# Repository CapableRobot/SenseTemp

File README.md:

# SenseTemp

Designed by [Capable Robot Components](http://capablerobot.com).  
Follow us on [Twitter](http://twitter.com/capablerobot) for product announcements and updates.

---

**SenseTemp is available on [CrowdSupply](https://www.crowdsupply.com/capable-robot-components/sensetemp) & [Mouser](https://www.mouser.com/Search/Refine?Keyword=sensetemp).  Please visit the [campaign page](https://www.crowdsupply.com/capable-robot-components/sensetemp) or [Mouser](https://www.mouser.com/ProductDetail/Crowd-Supply/cs-sensetemp-01?qs=sGAEpiMZZMsSgQ5oX0A7uhzs7btMGoRQjdDbb5Xc%2F1l7fRq91ffQkQ%3D%3D) for product information and to purchase SenseTemp.** 

SenseTemp provides four highly accurate and flexible temperature sensors which allow you to understand the operation of your:

* Mobile robot
* Embedded system 
* Double pane windows on your house
* Home brewing operation
* Or any other system where temperature and thermal conduction is important

It's designed for quick tests as well as long-duration process monitoring.

## SenseTemp Features 

* **Small:** so that it can be on a mobile system being tested.  The RTDs themselves are 2 mm x 4 mm, making them thermally responsive and great for measurement of point heat sources
* **Inexpensive:** allowing many points of temperature monitoring
* **Battery Powered:** including LiPoly & USB power banks
* **Wireless:** to make test setup faster and more flexible
* **Open Software:** so that the device can directly feed data into a data logging system of your choice
* **Open Hardware:** to enable derivative designs and for easy hacking

## Specifications

|Feature|Specification|
|----|----|
|Sensors|4x Platinum resistance temperature detectors (RTDs)|
|RTD Accuracy|±0.15°C|
|Temperature Range|-50°C to 260°C|
|Interface ICs|4x [MAX31865](https://www.maximintegrated.com/en/products/sensors/MAX31865.html) with 4 wire sensing|
|Form Factor|[Adafruit Feather](https://www.adafruit.com/feather)|
|Dimensions|0.9" x 2.4"|

## Feather Hosts

SenseTemp is designed to mate with Adafruit Feather-compatible host modules, like:

* [Adafruit Feather M4 Express](https://www.adafruit.com/product/3857)
* [Adafruit Feather M0 Express](https://www.adafruit.com/product/3403)
* [Adafruit ESP32 Feather Host](https://www.adafruit.com/product/3405)
* [Adafruit HalloWing](https://www.adafruit.com/product/3900)

Note that the ES8266 Feather is **NOT** supported due to the limited IO on the ESP8266.  It does not have enough pins to support the four SPI devices of the SenseTemp.

## Software

The software running on the Feather host processor does change based on the feather host you are using.  This repository contains software for:

* [**CircuitPython:**](software-circuitpython) if you are using a Cortex M4 or M0 Feather.  
* [**MicroPython:**](software-micropython) if you are using an ESP32 Feather.  The ESP32 is not currently supported by CircuitPython.

## Hardware Revisions

* [CREAES](revisions/CREAES) : Last release 2018-10-18.
	* Changed from 0805 to 0603 passive components.
	* Moved all components to top side of PCB.
	* Changed license from **CC BY-SA 4.0** to **CERN OHL v1.2**.
	* Can be powered from either USB or Li-Ion sources.
* [X9EG](revisions/X9EG) : Released 2018-08-28.
	* Added `SIO` pin with AT21CS01 1-Wire EEPROM for configuration & serialization.
	* Added `EN` pin to allow host PCB to disable 5v to 3v regulator on this PCB.
	* Changed RTD connector from 20 pin (used on XTMT version) to 16 pin.
* [XTMT](revisions/XTMT) : Initial version released 2018-05-18.

## License Information

| **Type** | **License** |
| --- | --- |
| Hardware | Copyright Capable Robot Components 2018 <br><br>This documentation describes Open Hardware and is licensed under the [CERN OHL v1.2 or later](https://www.ohwr.org/licenses/cern-ohl/license_versions/v1.2). <br/><br/> You may redistribute and modify this documentation under the terms of the CERN OHL v.1.2.  This documentation is distributed WITHOUT ANY EXPRESS OR IMPLIED WARRANTY, INCLUDING OF MERCHANTABILITY, SATISFACTORY QUALITY AND FITNESS FOR A PARTICULAR PURPOSE. Please see the CERN OHL v.1.2 for applicable conditions |
| Software | [MIT License](LICENSE.txt) |
| Documentation | [Creative Commons Attribution-ShareAlike](https://creativecommons.org/licenses/by-sa/4.0/) License |

More detailed information about the CERN License is available in the [license](license) folder and on the [CERN website](https://www.ohwr.org/projects/cernohl/wiki).

| **OSHW Certification** |
| --- |
|  | 
| [Certified open source hardware](https://certification.oshwa.org/us000151.html) by the [Open Source Hardware Association](https://www.oshwa.org) |

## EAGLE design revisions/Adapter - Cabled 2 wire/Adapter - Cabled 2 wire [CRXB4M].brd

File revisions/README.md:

# SenseTemp Hardware Revisions

Designed by [Capable Robot Components](http://capablerobot.com).  
Follow us on [Twitter](http://twitter.com/capablerobot) for product announcements and updates.

---

**SenseTemp is available on [CrowdSupply](https://www.crowdsupply.com/capable-robot-components/sensetemp) & [Mouser](https://www.mouser.com/Search/Refine?Keyword=sensetemp).  Please visit the [campaign page](https://www.crowdsupply.com/capable-robot-components/sensetemp) or [Mouser](https://www.mouser.com/ProductDetail/Crowd-Supply/cs-sensetemp-01?qs=sGAEpiMZZMsSgQ5oX0A7uhzs7btMGoRQjdDbb5Xc%2F1l7fRq91ffQkQ%3D%3D) for product information and to purchase SenseTemp.** 

---

* [CREAES](revisions/CREAES) : Last release 2018-10-18.
	* Changed from 0805 to 0603 passive components.
	* Moved all components to top side of PCB.
	* Changed license from **CC BY-SA 4.0** to **CERN OHL v1.2**.
	* Can be powered from either USB or Li-Ion sources.
* [X9EG](revisions/X9EG) : Released 2018-08-28.
	* Added `SIO` pin with AT21CS01 1-Wire EEPROM for configuration & serialization.
	* Added `EN` pin to allow host PCB to disable 5v to 3v regulator on this PCB.
	* Changed RTD connector from 20 pin (used on XTMT version) to 16 pin.
* [XTMT](revisions/XTMT) : Initial version released 2018-05-18.

---

Also in this folder are two adapter PCBs which allows SenseTemp's 50mil (4x 4-wire) connector to be adapted to 4x 2-way 5mm screw terminals, allowing SenseTemp to use 2-wire and 3-wire (in 2-wire mode) P1000 RTDs.

The 'stacking' design has the same outline and mounting as SenseTemp and is designed to stack vertically above SenseTemp using a [AMP Minitek 20021321-00016C4LF](https://octopart.com/20021321-00016c4lf-amphenol+icc+%2F+fci-12642443?r=sp) (or similar) connector.

The 'cabled' design is smaller and cabled to SenseTemp via a 16 conductor, 50 mil ribbon cabled.  The recommended 16 pin connector for it is [CNC Tech 3221-16-0300-00](https://octopart.com/3221-16-0300-00-cnc+tech-47114357?r=sp) or similar.

Bare PCBs (e.g. no components installed or included) are available for purchase directly from OSHPark:

| [Cabled Adapter](https://oshpark.com/shared_projects/WjlpBAlQ) | [Stacking Adapter](https://oshpark.com/shared_projects/11pGTiwa) |
|---|---|
||  |

---

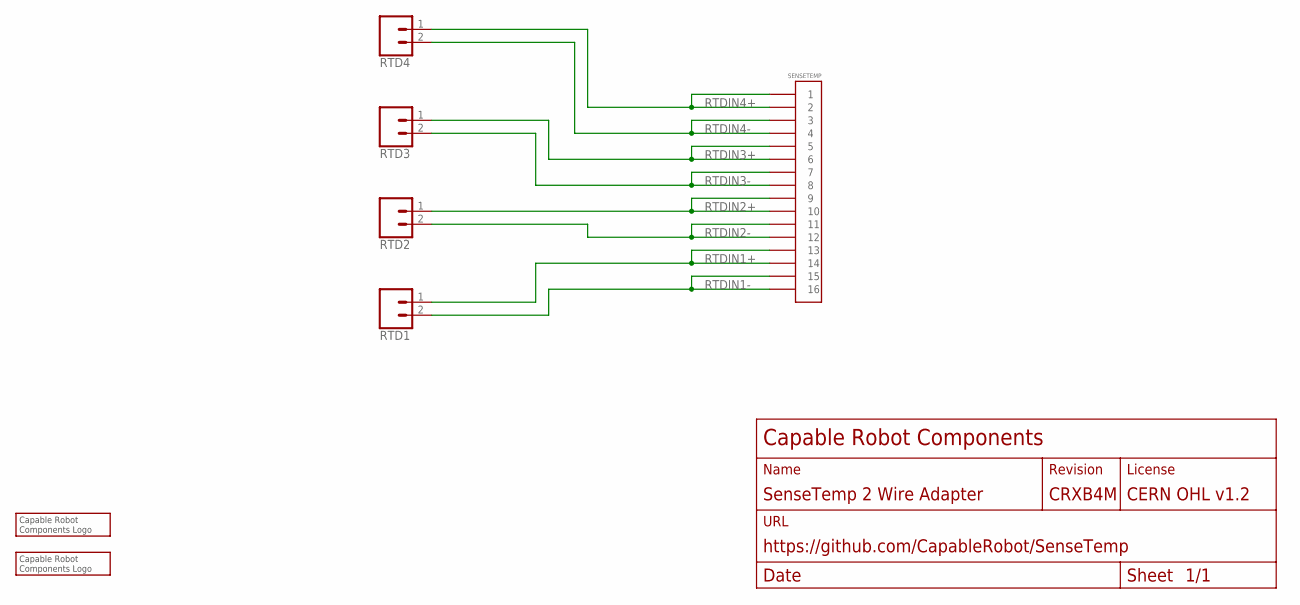
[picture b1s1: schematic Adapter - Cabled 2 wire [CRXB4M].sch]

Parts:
LOGO1: CRC-LOGO7SILK; CRC-LOGO-7-SILK
LOGO2: CRC-LOGO5; CRC-LOGO-5
RTD1, RTD2, RTD3, RTD4: CONN_025MM; SCREWTERMINAL-5MM-2
SENSETEMP: CONN-16ZT; CONN-2X8-050-SMT-ZT; MPN 3221-16-0300-00

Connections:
RTDIN1+: RTD1.1, SENSETEMP.13, SENSETEMP.14
RTDIN1-: RTD1.2, SENSETEMP.15, SENSETEMP.16
RTDIN2+: RTD2.1, SENSETEMP.9, SENSETEMP.10
RTDIN2-: RTD2.2, SENSETEMP.11, SENSETEMP.12
RTDIN3+: RTD3.1, SENSETEMP.5, SENSETEMP.6
RTDIN3-: RTD3.2, SENSETEMP.7, SENSETEMP.8
RTDIN4+: RTD4.1, SENSETEMP.1, SENSETEMP.2
RTDIN4-: RTD4.2, SENSETEMP.3, SENSETEMP.4

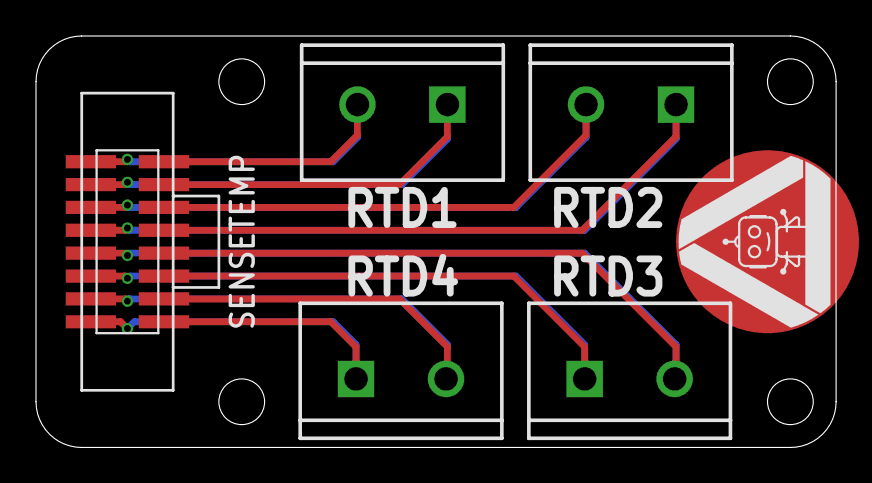
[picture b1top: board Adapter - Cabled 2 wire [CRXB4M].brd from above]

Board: 2 copper layers, 44.5 x 22.9 mm, 7 parts (1 on the bottom side), 8 nets.

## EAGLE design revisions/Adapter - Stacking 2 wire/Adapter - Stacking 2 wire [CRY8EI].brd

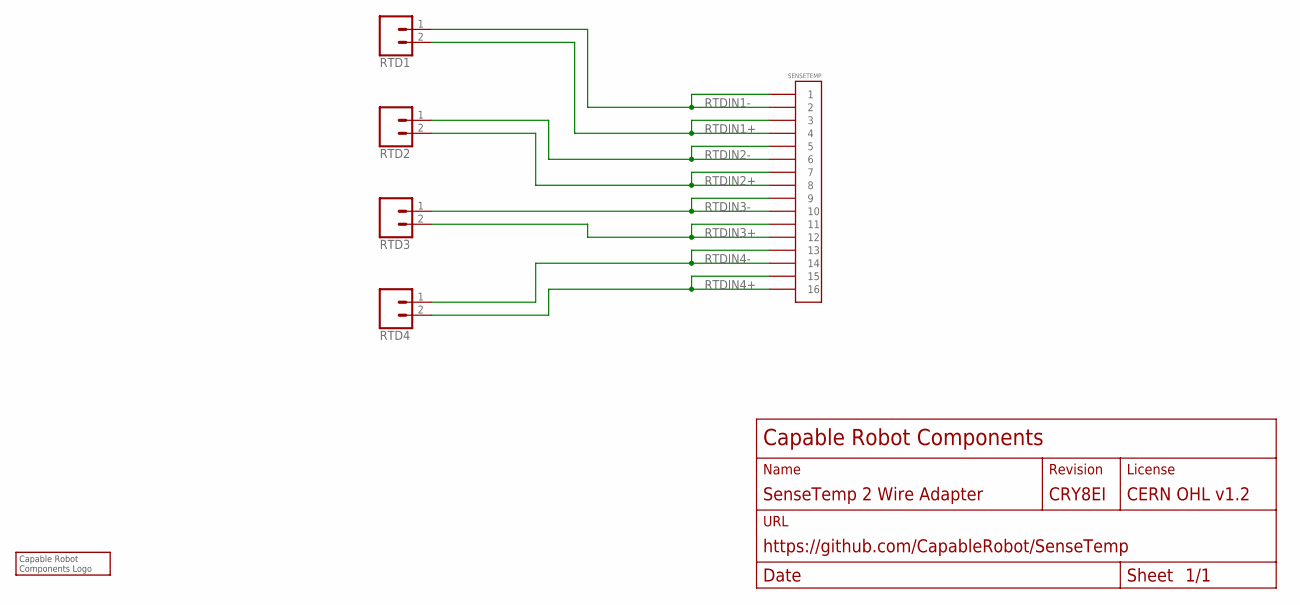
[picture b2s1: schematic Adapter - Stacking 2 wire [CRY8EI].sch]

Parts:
LOGO1: CRC-LOGO7SILK; CRC-LOGO-7-SILK
RTD1, RTD2, RTD3, RTD4: CONN_025MM; SCREWTERMINAL-5MM-2
SENSETEMP: CONN-16ZT; CONN-2X8-050-SMT-ZT; MPN 3221-16-0300-00

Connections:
RTDIN1+: RTD1.2, SENSETEMP.3, SENSETEMP.4
RTDIN1-: RTD1.1, SENSETEMP.1, SENSETEMP.2
RTDIN2+: RTD2.2, SENSETEMP.7, SENSETEMP.8
RTDIN2-: RTD2.1, SENSETEMP.5, SENSETEMP.6
RTDIN3+: RTD3.2, SENSETEMP.11, SENSETEMP.12
RTDIN3-: RTD3.1, SENSETEMP.9, SENSETEMP.10
RTDIN4+: RTD4.2, SENSETEMP.15, SENSETEMP.16
RTDIN4-: RTD4.1, SENSETEMP.13, SENSETEMP.14

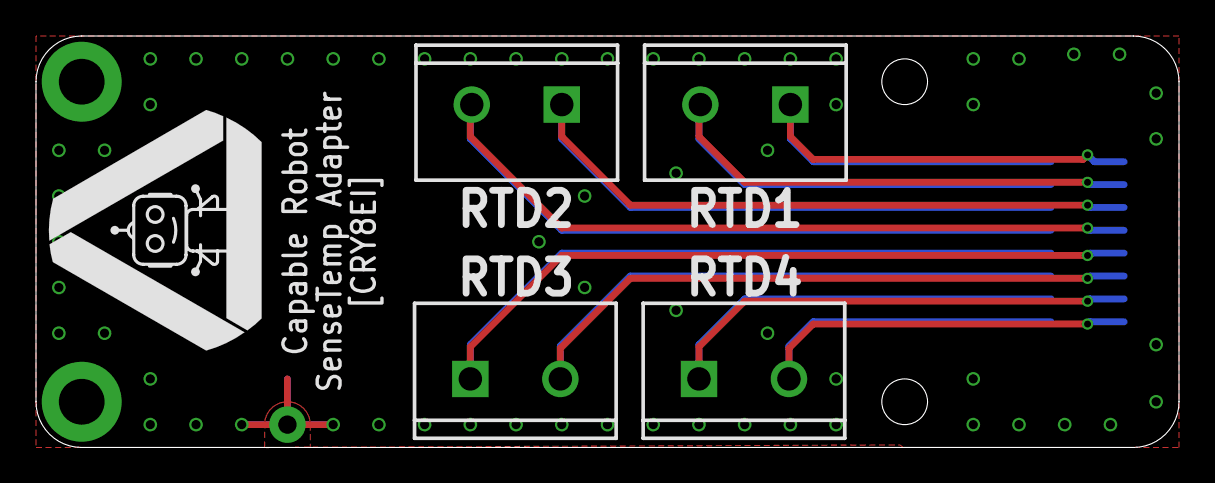
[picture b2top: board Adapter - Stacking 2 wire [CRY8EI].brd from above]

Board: 2 copper layers, 63.5 x 22.9 mm, 6 parts (1 on the bottom side), 8 nets.

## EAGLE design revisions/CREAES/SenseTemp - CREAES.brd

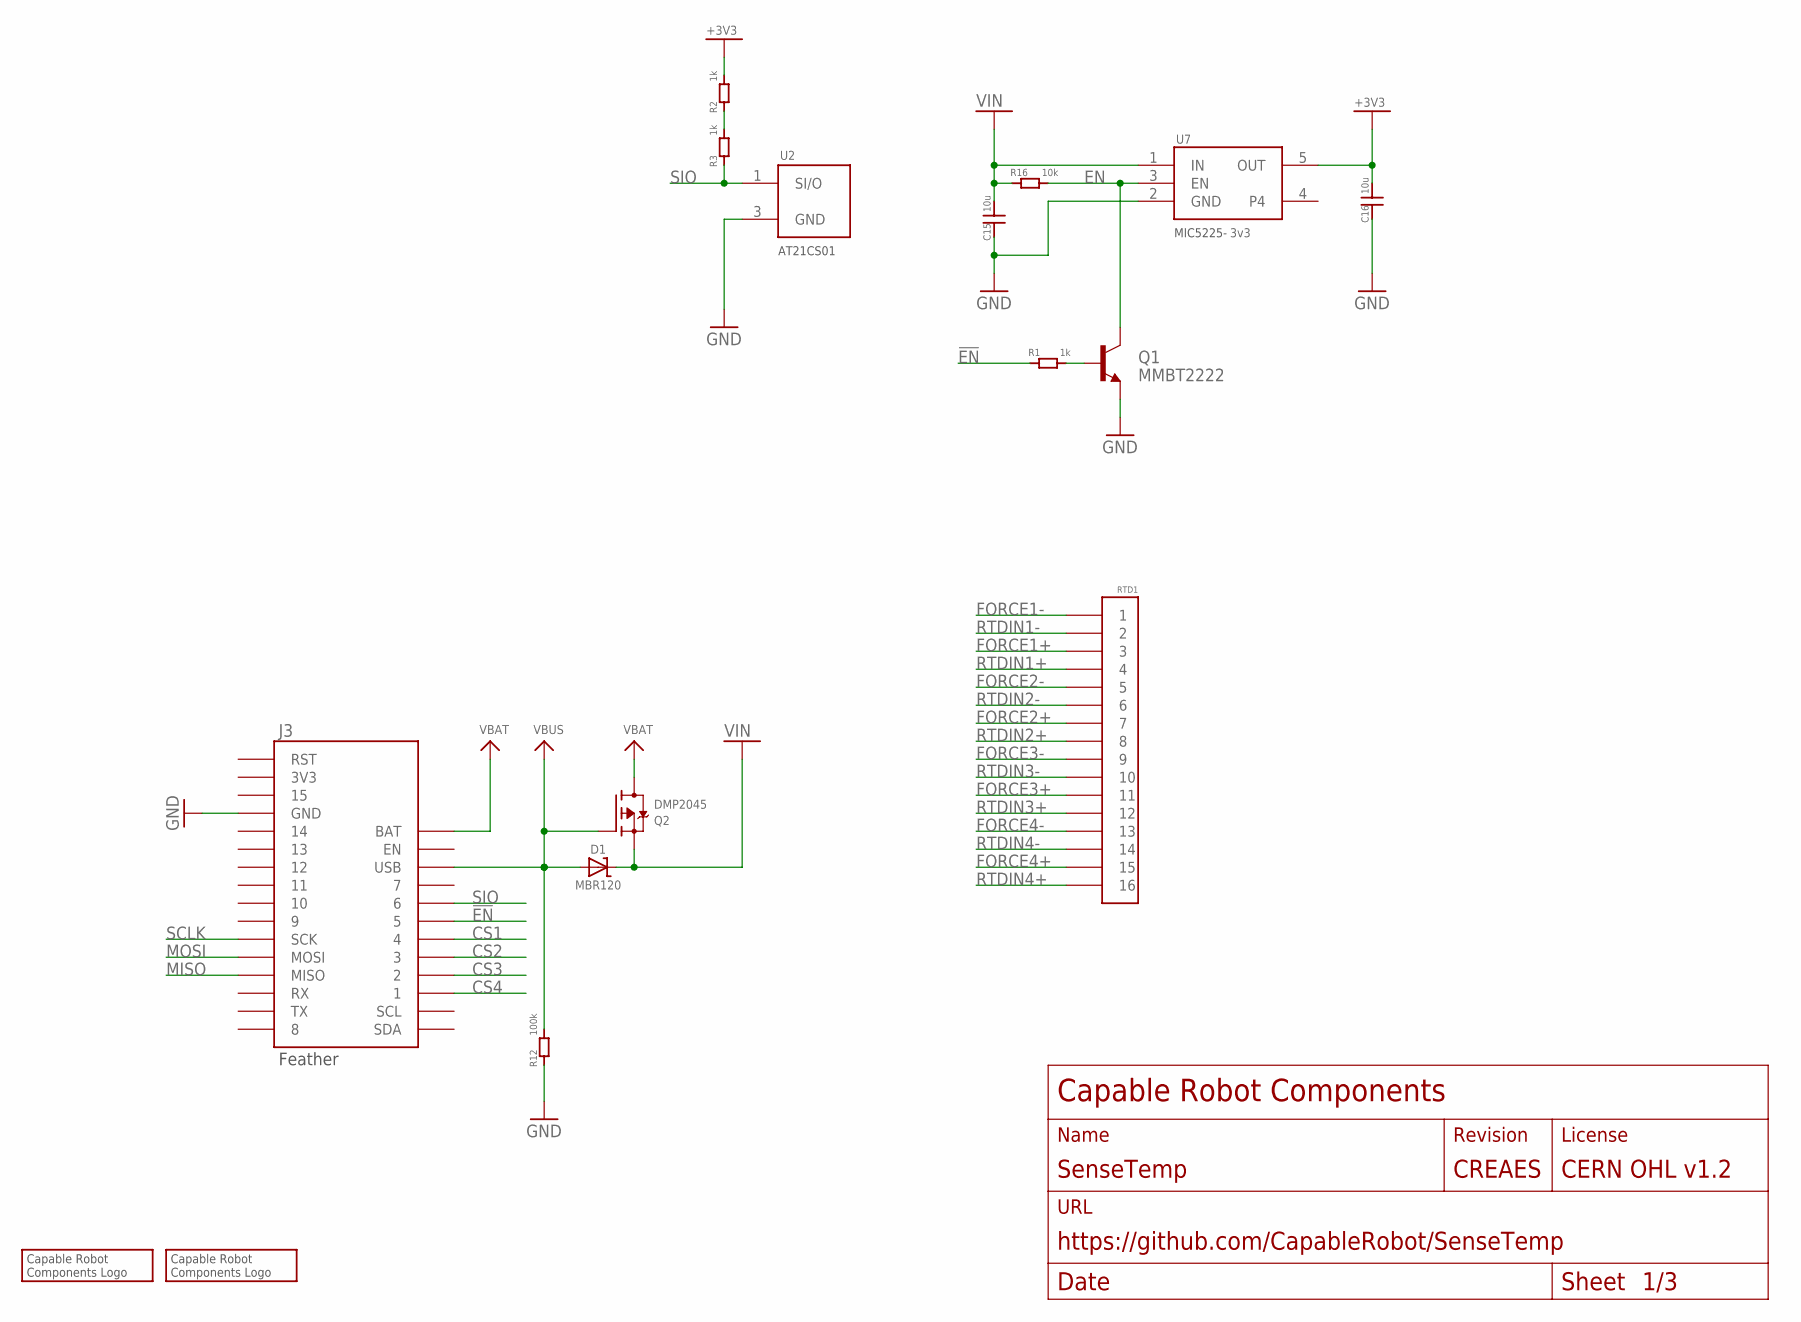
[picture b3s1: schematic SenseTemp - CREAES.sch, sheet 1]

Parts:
C15, C16: 10u; 0805
D1: MBR120; SOD-123; MPN MBR120VLSFT3G
J3: FEATHERPTH; FEATHER-PTH
LOGO1: CRC-LOGO7SILK; CRC-LOGO-7-SILK
LOGO2: CRC-LOGO5; CRC-LOGO-5
Q1: MMBT2222; SOT23-3; MPN MMBT2222LT1G
Q2: DMP2045; SOT23-R; MPN DMP2045U-7
R1, R2, R3: 1k; 0603
R12: 100k; 0603
R16: 10k; 0603
RTD1: CONN-16ZT; CONN-2X8-050-SMT-ZT; MPN 3221-16-0300-00
U2: AT21CS01; SOT23
U7: 3v3; SOT25

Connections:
!EN: J3.5, R1.1
+3V3: C16.2, R2.2, U7.5 (OUT); also elsewhere on the board
CS1: J3.4; also elsewhere on the board
CS2: J3.3; also elsewhere on the board
CS3: J3.2; also elsewhere on the board
CS4: J3.1; also elsewhere on the board
EN: Q1.3 (C), R16.2, U7.3 (EN)
FORCE1+: RTD1.3; also elsewhere on the board
FORCE1-: RTD1.1; also elsewhere on the board
FORCE2+: RTD1.7; also elsewhere on the board
FORCE2-: RTD1.5; also elsewhere on the board
FORCE3+: RTD1.11; also elsewhere on the board
FORCE3-: RTD1.9; also elsewhere on the board
FORCE4+: RTD1.15; also elsewhere on the board
FORCE4-: RTD1.13; also elsewhere on the board
GND: C15.1, C16.1, J3.GND, Q1.2 (E), R12.1, U2.3 (GND), U7.2 (GND); also elsewhere on the board
MISO: J3.MISO; also elsewhere on the board
MOSI: J3.MOSI; also elsewhere on the board
unnamed: R2.1, R3.2
unnamed: Q1.1 (B), R1.2
RTDIN1+: RTD1.4; also elsewhere on the board
RTDIN1-: RTD1.2; also elsewhere on the board
RTDIN2+: RTD1.8; also elsewhere on the board
RTDIN2-: RTD1.6; also elsewhere on the board
RTDIN3+: RTD1.12; also elsewhere on the board
RTDIN3-: RTD1.10; also elsewhere on the board
RTDIN4+: RTD1.16; also elsewhere on the board
RTDIN4-: RTD1.14; also elsewhere on the board
SCLK: J3.SCK; also elsewhere on the board
SIO: J3.6, R3.1, U2.1 (SI/O)
VBAT: J3.BAT, Q2.3 (D)
VBUS: D1.A, J3.USB, Q2.1 (G), R12.2
VIN: C15.2, D1.C, Q2.2 (S), R16.1, U7.1 (IN)

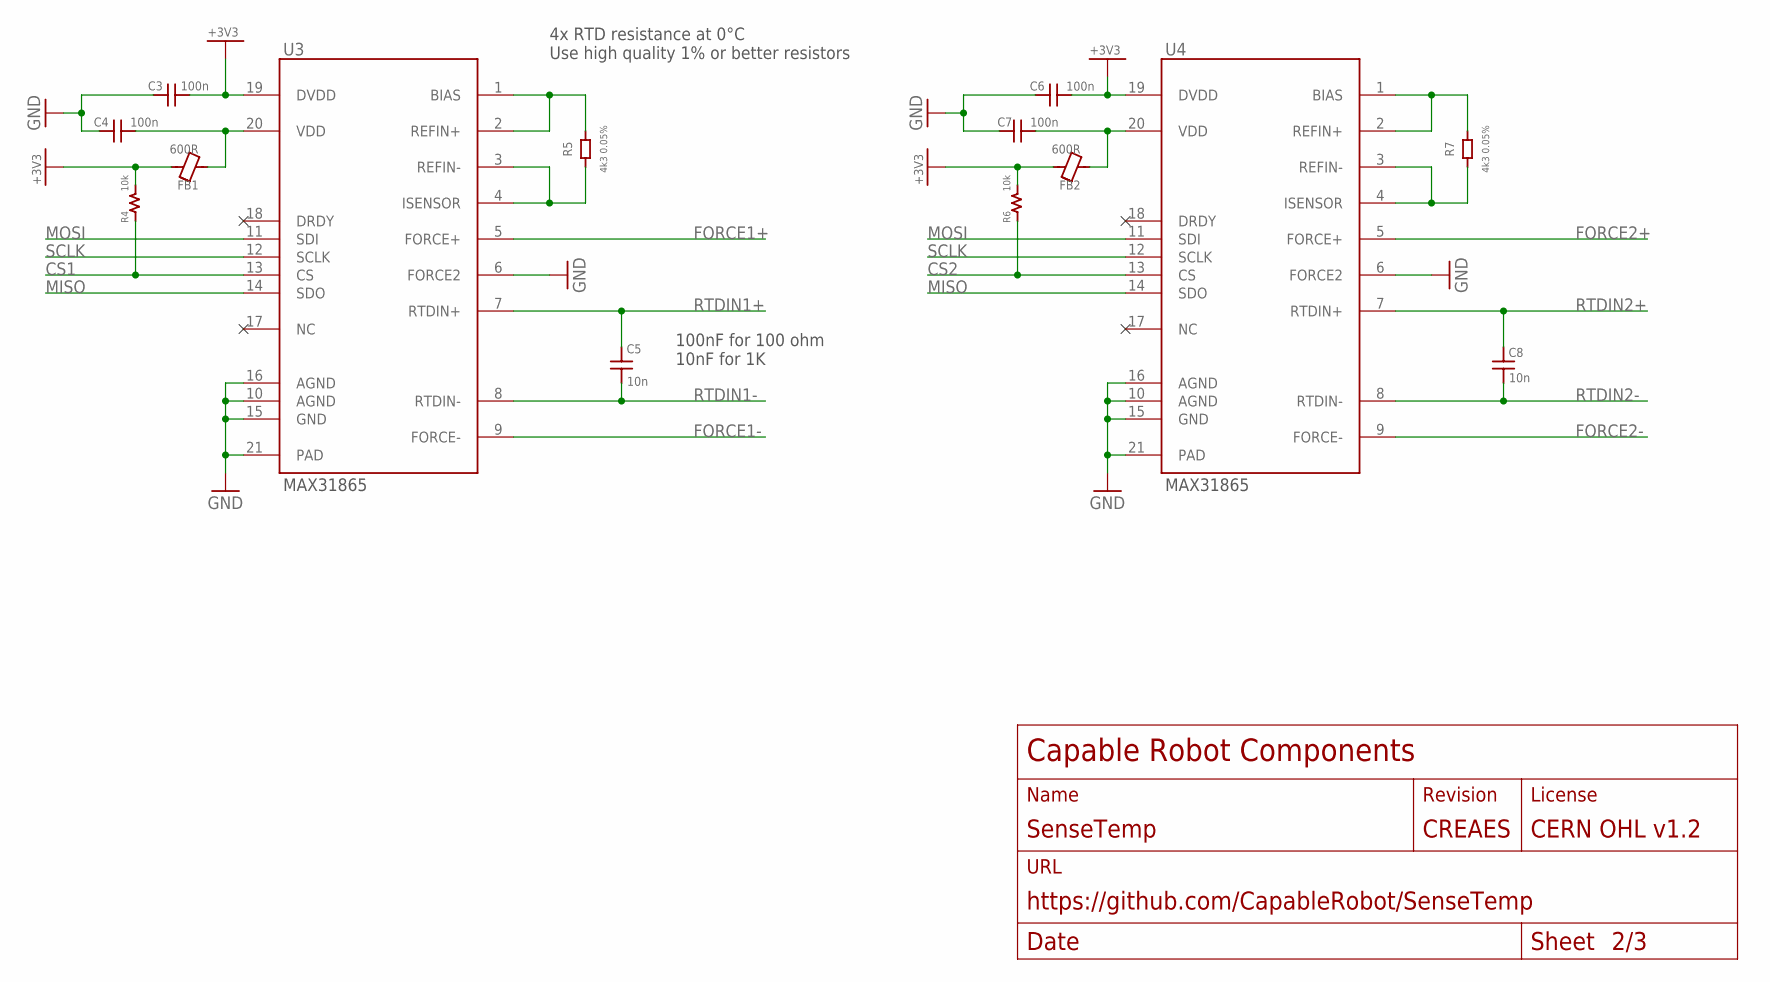
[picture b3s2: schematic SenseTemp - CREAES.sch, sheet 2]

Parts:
C3, C4, C6, C7: 100n; 0603
C5, C8: 10n; 0603
FB1, FB2: 600R; 0603
R4, R6: 10k; 0603
R5, R7: 4k3 0.05%; 0603
U3, U4: MAX31865; QFN65P500X500X100-21T325

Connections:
+3V3: C3.1, C6.1, FB1.2, FB2.2, R4.2, R6.2, U3.19 (DVDD), U4.19 (DVDD); also elsewhere on the board
CS1: R4.1, U3.13 (CS); also elsewhere on the board
CS2: R6.1, U4.13 (CS); also elsewhere on the board
FORCE1+: U3.5 (FORCE+); also elsewhere on the board
FORCE1-: U3.9 (FORCE-); also elsewhere on the board
FORCE2+: U4.5 (FORCE+); also elsewhere on the board
FORCE2-: U4.9 (FORCE-); also elsewhere on the board
GND: C3.2, C4.2, C6.2, C7.2, U3.6 (FORCE2), U3.10 (AGND), U3.15 (GND), U3.16 (AGND), U3.21 (PAD), U4.6 (FORCE2), U4.10 (AGND), U4.15 (GND), U4.16 (AGND), U4.21 (PAD); also elsewhere on the board
MISO: U3.14 (SDO), U4.14 (SDO); also elsewhere on the board
MOSI: U3.11 (SDI), U4.11 (SDI); also elsewhere on the board
unnamed: R5.2, U3.1 (BIAS), U3.2 (REFIN+)
unnamed: R5.1, U3.3 (REFIN-), U3.4 (ISENSOR)
unnamed: C4.1, FB1.1, U3.20 (VDD)
unnamed: R7.2, U4.1 (BIAS), U4.2 (REFIN+)
unnamed: R7.1, U4.3 (REFIN-), U4.4 (ISENSOR)
unnamed: C7.1, FB2.1, U4.20 (VDD)
RTDIN1+: C5.1, U3.7 (RTDIN+); also elsewhere on the board
RTDIN1-: C5.2, U3.8 (RTDIN-); also elsewhere on the board
RTDIN2+: C8.1, U4.7 (RTDIN+); also elsewhere on the board
RTDIN2-: C8.2, U4.8 (RTDIN-); also elsewhere on the board
SCLK: U3.12 (SCLK), U4.12 (SCLK); also elsewhere on the board

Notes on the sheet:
4x RTD resistance at 0°C Use high quality 1% or better resistors
100nF for 100 ohm 10nF for 1K

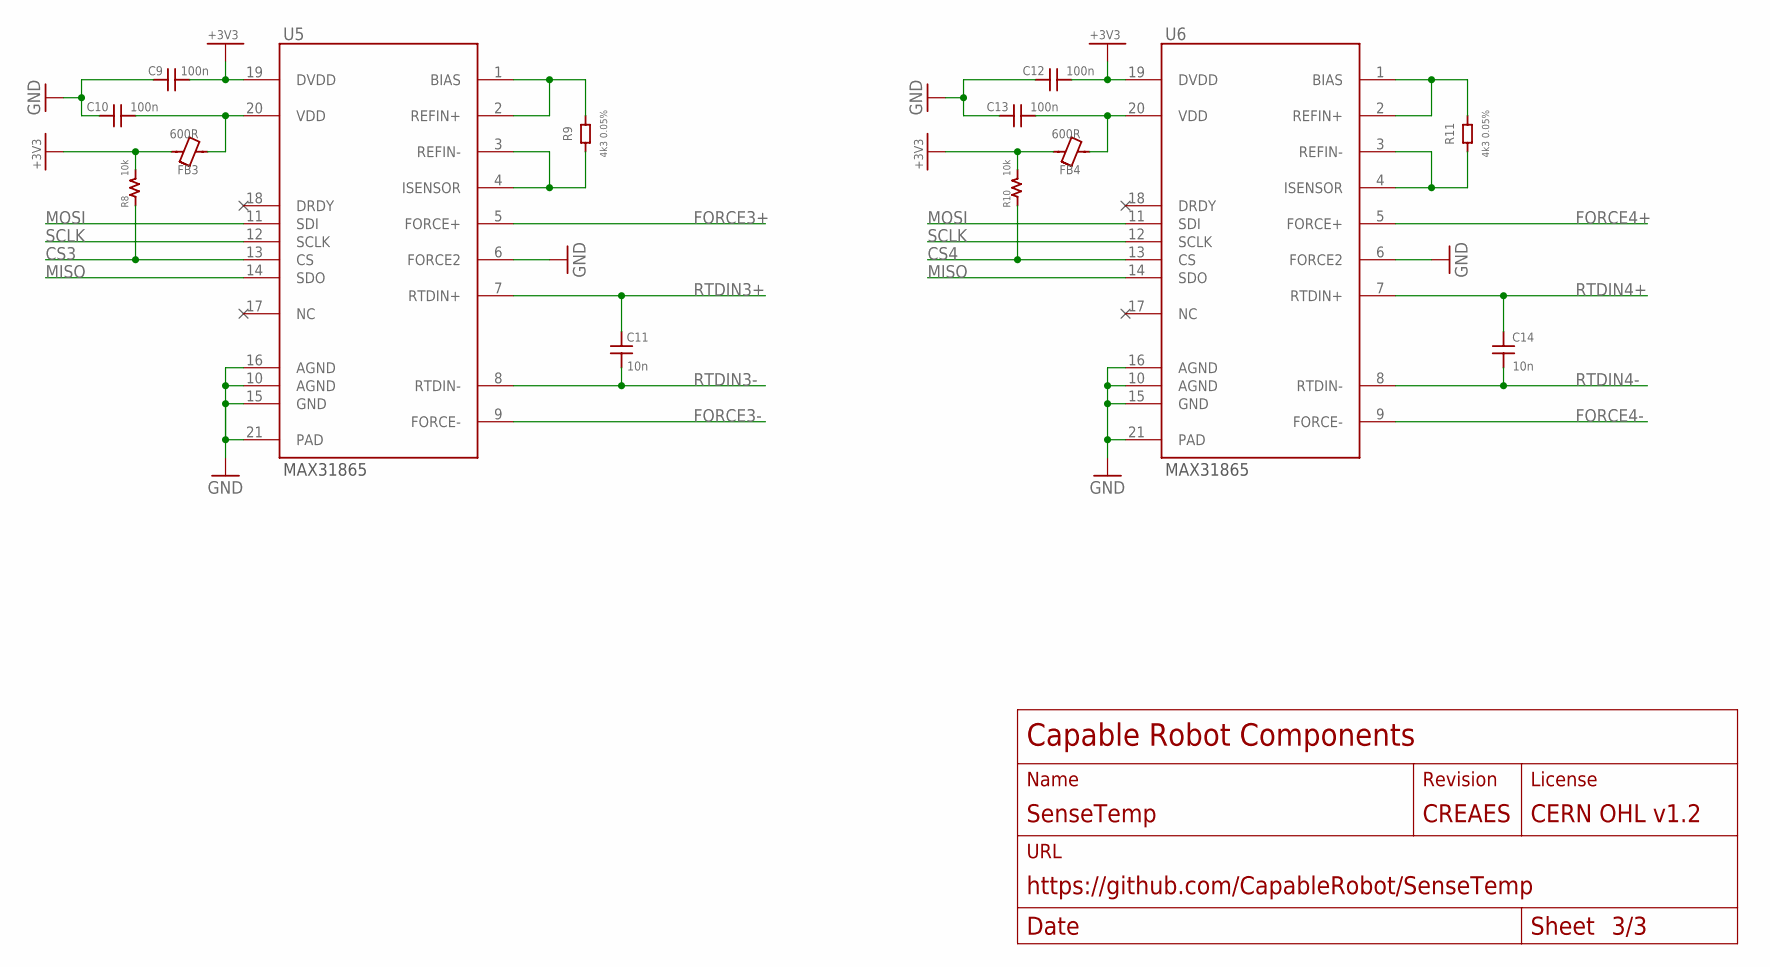
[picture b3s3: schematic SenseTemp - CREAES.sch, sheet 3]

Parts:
C9, C10, C12, C13: 100n; 0603
C11, C14: 10n; 0603
FB3, FB4: 600R; 0603
R8, R10: 10k; 0603
R9, R11: 4k3 0.05%; 0603
U5, U6: MAX31865; QFN65P500X500X100-21T325

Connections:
+3V3: C9.1, C12.1, FB3.2, FB4.2, R8.2, R10.2, U5.19 (DVDD), U6.19 (DVDD); also elsewhere on the board
CS3: R8.1, U5.13 (CS); also elsewhere on the board
CS4: R10.1, U6.13 (CS); also elsewhere on the board
FORCE3+: U5.5 (FORCE+); also elsewhere on the board
FORCE3-: U5.9 (FORCE-); also elsewhere on the board
FORCE4+: U6.5 (FORCE+); also elsewhere on the board
FORCE4-: U6.9 (FORCE-); also elsewhere on the board
GND: C9.2, C10.2, C12.2, C13.2, U5.6 (FORCE2), U5.10 (AGND), U5.15 (GND), U5.16 (AGND), U5.21 (PAD), U6.6 (FORCE2), U6.10 (AGND), U6.15 (GND), U6.16 (AGND), U6.21 (PAD); also elsewhere on the board
MISO: U5.14 (SDO), U6.14 (SDO); also elsewhere on the board
MOSI: U5.11 (SDI), U6.11 (SDI); also elsewhere on the board
unnamed: R9.2, U5.1 (BIAS), U5.2 (REFIN+)
unnamed: R9.1, U5.3 (REFIN-), U5.4 (ISENSOR)
unnamed: C10.1, FB3.1, U5.20 (VDD)
unnamed: R11.2, U6.1 (BIAS), U6.2 (REFIN+)
unnamed: R11.1, U6.3 (REFIN-), U6.4 (ISENSOR)
unnamed: C13.1, FB4.1, U6.20 (VDD)
RTDIN3+: C11.1, U5.7 (RTDIN+); also elsewhere on the board
RTDIN3-: C11.2, U5.8 (RTDIN-); also elsewhere on the board
RTDIN4+: C14.1, U6.7 (RTDIN+); also elsewhere on the board
RTDIN4-: C14.2, U6.8 (RTDIN-); also elsewhere on the board
SCLK: U5.12 (SCLK), U6.12 (SCLK); also elsewhere on the board

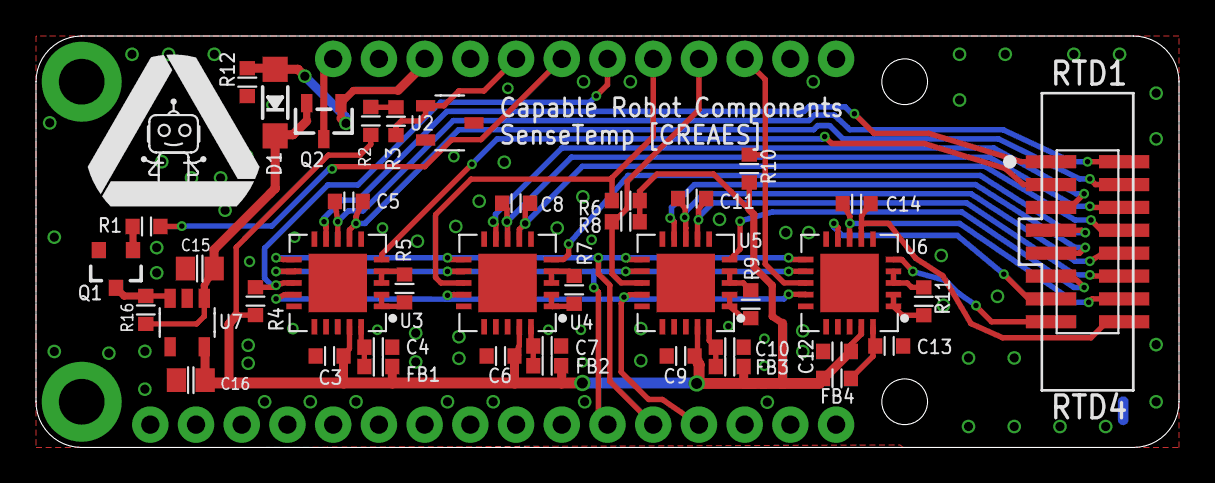
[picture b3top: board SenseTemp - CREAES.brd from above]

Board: 2 copper layers, 63.5 x 22.9 mm, 44 parts (1 on the bottom side), 45 nets.

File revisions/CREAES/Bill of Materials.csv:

Name,Mpn,Count,Device,Value,Package,Mfg,Cost,Description
"C15,C16",CL21A106KPFNNNE,2,CAP-0805,10u,0805,Samsung,0.1088,""
"C3,C4,C6,C7,C9,C10,C12,C13",MF-CAP-0603-0.1uF,8,CAP-0603,100n,0603,Generic,,""
"C5,C8,C11,C14",MF-CAP-0603-0.01uF,4,CAP-0603,10n,0603,Generic,,""
D1,MBR120VLSFT3G,1,DIODE-SCHOTTKY-SOD-123,MBR120,SOD-123,ON Semiconductor,0.16,""
"FB1,FB2,FB3,FB4",BK1608HW601-T,4,FER-0603,600R,0603,Taiyo Yuden,0.11350000000000002,""
Q1,MMBT2222LT1G,1,TRANSISTOR_NPN-SOT23-3,MMBT2222,SOT23-3,ON Semiconductor,0.0642,""
Q2,DMP2045U-7,1,MOSFET-P,DMP2045,SOT23-R,Diodes Inc.,0.124,""
"R1,R2,R3",MF-RES-0603-1K,3,RES-0603,1k,0603,Generic,,""
R12,MF-RES-0603-100K,1,RES-0603,100k,0603,Generic,,""
"R4,R6,R8,R10,R16",MF-RES-0603-10K,5,RES-0603,10k,0603,Generic,,""
"R5,R7,R9,R11",ERA3ARW432V,4,RES-0603,4k3 0.05%,0603,Panasonic,1.7916,""
RTD1,3221-16-0300-00,1,CONN-16-ZT,,CONN-2X8-050-SMT-ZT,CNC Tech,0.946,""
U2,AT21CS01-STUM10-T,1,AT21CS01,,SOT23,Microchip,0.1836,""
"U3,U4,U5,U6",MAX31865ATP+,4,MAX31865,,QFN65P500X500X100-21T325,Maxim Integrated,12.336,""
U7,AP2112K-3.3TRG1,1,MIC5225,3v3,SOT25,Diodes Inc.,0.15,""

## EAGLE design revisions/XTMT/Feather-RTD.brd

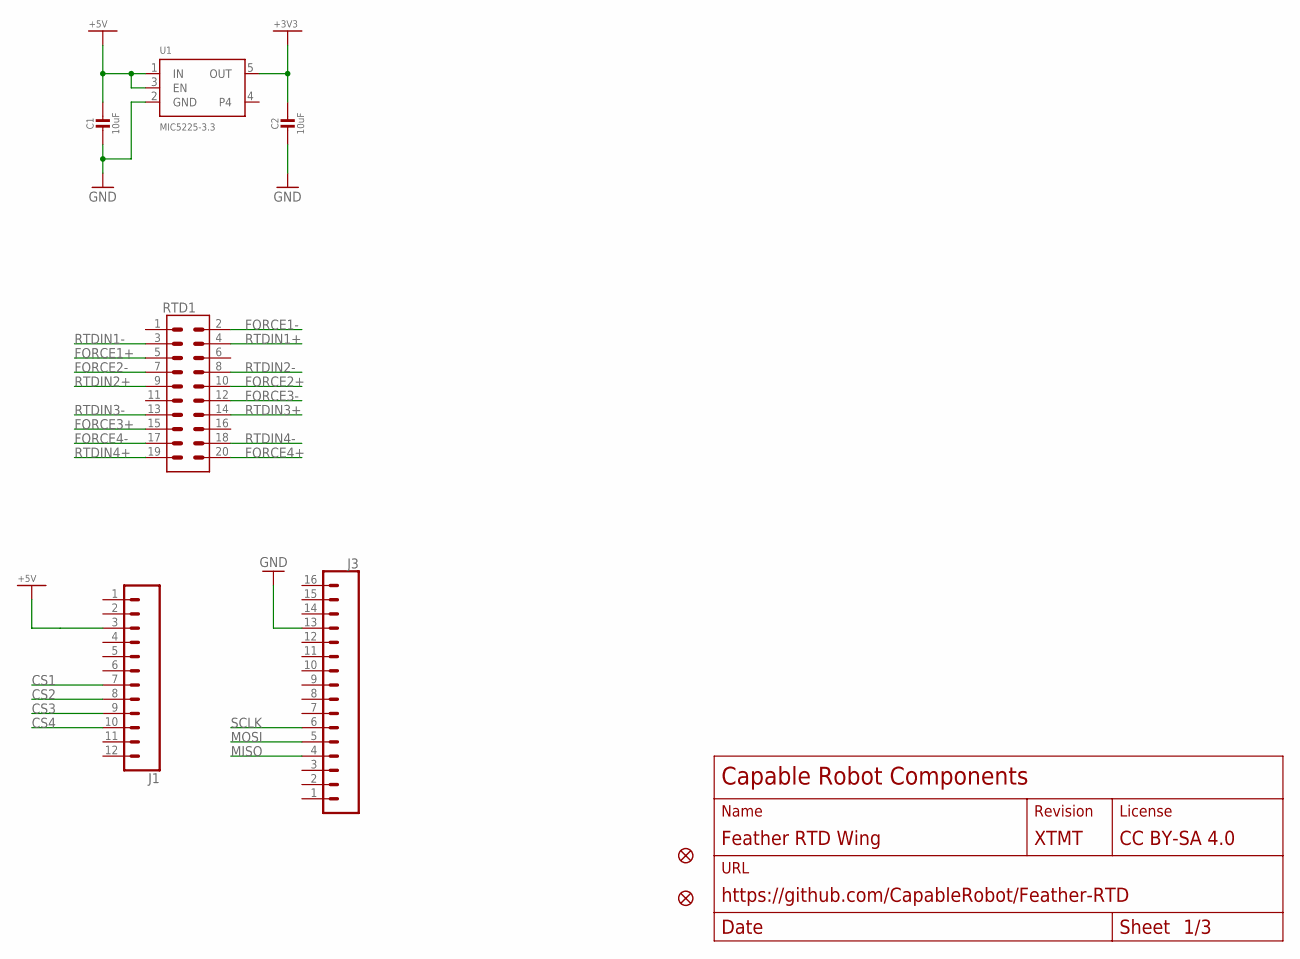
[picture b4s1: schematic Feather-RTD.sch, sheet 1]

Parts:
C1, C2: 10uF; 0805-NO
FID1, FID2: FIDUCIAL""; FIDUCIAL_1MM
J1: CONN_12NO_SILK; 1X12_NO_SILK
J3: CONN_161X16_NO_SILK; 1X16_NO_SILK
RTD1: CONN-20; CONN-2X10-050-SMT-ZT
U1: MIC5225-3.3; SOT23-5

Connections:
+3V3: C2.1, U1.5 (OUT); also elsewhere on the board
+5V: C1.1, J1.3, U1.1 (IN), U1.3 (EN)
CS1: J1.7; also elsewhere on the board
CS2: J1.8; also elsewhere on the board
CS3: J1.9; also elsewhere on the board
CS4: J1.10; also elsewhere on the board
FORCE1+: RTD1.5; also elsewhere on the board
FORCE1-: RTD1.2; also elsewhere on the board
FORCE2+: RTD1.10; also elsewhere on the board
FORCE2-: RTD1.7; also elsewhere on the board
FORCE3+: RTD1.15; also elsewhere on the board
FORCE3-: RTD1.12; also elsewhere on the board
FORCE4+: RTD1.20; also elsewhere on the board
FORCE4-: RTD1.17; also elsewhere on the board
GND: C1.2, C2.2, J3.13, U1.2 (GND); also elsewhere on the board
MISO: J3.4; also elsewhere on the board
MOSI: J3.5; also elsewhere on the board
RTDIN1+: RTD1.4; also elsewhere on the board
RTDIN1-: RTD1.3; also elsewhere on the board
RTDIN2+: RTD1.9; also elsewhere on the board
RTDIN2-: RTD1.8; also elsewhere on the board
RTDIN3+: RTD1.14; also elsewhere on the board
RTDIN3-: RTD1.13; also elsewhere on the board
RTDIN4+: RTD1.19; also elsewhere on the board
RTDIN4-: RTD1.18; also elsewhere on the board
SCLK: J3.6; also elsewhere on the board

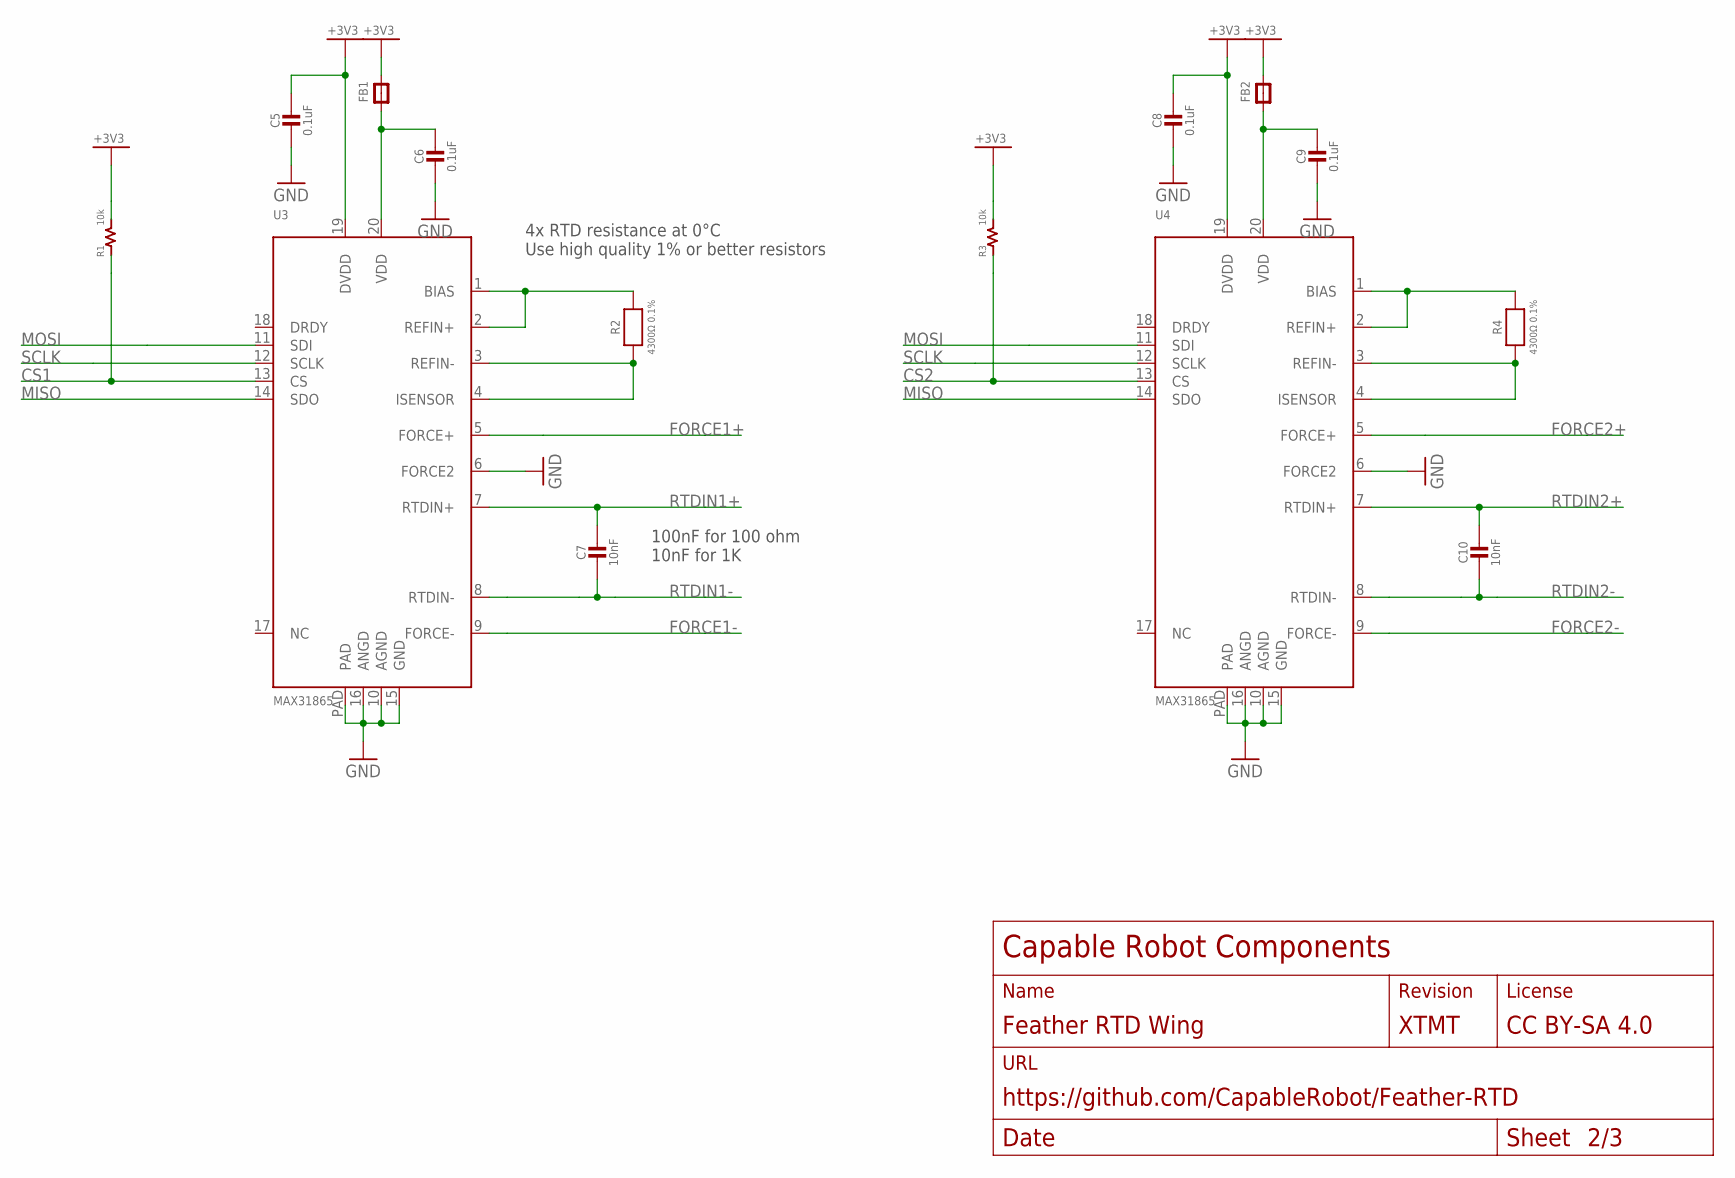
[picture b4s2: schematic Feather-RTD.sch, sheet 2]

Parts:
C5, C6, C8, C9: 0.1uF; 0805-NO
C7, C10: 10nF; 0805-NO
FB1, FB2: FERRITE-0805NO; 0805-NO
R1, R3: 10k; 0603
R2, R4: 4300Ω 0.1%; 0805-NO
U3, U4: MAX31865; QFN20_4MM_0.65MM

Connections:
+3V3: C5.1, C8.1, FB1.2, FB2.2, R1.2, R3.2, U3.19 (DVDD), U4.19 (DVDD); also elsewhere on the board
CS1: R1.1, U3.13 (CS); also elsewhere on the board
CS2: R3.1, U4.13 (CS); also elsewhere on the board
FORCE1+: U3.5 (FORCE+); also elsewhere on the board
FORCE1-: U3.9 (FORCE-); also elsewhere on the board
FORCE2+: U4.5 (FORCE+); also elsewhere on the board
FORCE2-: U4.9 (FORCE-); also elsewhere on the board
GND: C5.2, C6.2, C8.2, C9.2, U3.6 (FORCE2), U3.10 (AGND), U3.15 (GND), U3.16 (ANGD), U3.PAD, U4.6 (FORCE2), U4.10 (AGND), U4.15 (GND), U4.16 (ANGD), U4.PAD; also elsewhere on the board
MISO: U3.14 (SDO), U4.14 (SDO); also elsewhere on the board
MOSI: U3.11 (SDI), U4.11 (SDI); also elsewhere on the board
unnamed: R2.2, U3.1 (BIAS), U3.2 (REFIN+)
unnamed: R2.1, U3.3 (REFIN-), U3.4 (ISENSOR)
unnamed: C6.1, FB1.1, U3.20 (VDD)
unnamed: R4.2, U4.1 (BIAS), U4.2 (REFIN+)
unnamed: R4.1, U4.3 (REFIN-), U4.4 (ISENSOR)
unnamed: C9.1, FB2.1, U4.20 (VDD)
RTDIN1+: C7.1, U3.7 (RTDIN+); also elsewhere on the board
RTDIN1-: C7.2, U3.8 (RTDIN-); also elsewhere on the board
RTDIN2+: C10.1, U4.7 (RTDIN+); also elsewhere on the board
RTDIN2-: C10.2, U4.8 (RTDIN-); also elsewhere on the board
SCLK: U3.12 (SCLK), U4.12 (SCLK); also elsewhere on the board

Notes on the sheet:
4x RTD resistance at 0°C Use high quality 1% or better resistors
100nF for 100 ohm 10nF for 1K

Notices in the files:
revisions/Adapter - Cabled 2 wire/Adapter - Cabled 2 wire [CRXB4M].sch:
LICENSE: CERN OHL v1.2
revisions/XTMT/Feather-RTD.sch:
LICENSE: CC BY-SA 4.0
parts and their libraries:
SparkFun-Connectors: Licensing: Creative Commons ShareAlike 4.0 International - https://creativecommons.org/licenses/by-sa/4.0
microbuilder: This work is placed in the public domain, and may be freely used for commercial and non-commercial work with the following conditions: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
